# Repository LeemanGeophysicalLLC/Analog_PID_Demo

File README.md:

# Analog_PID_Demo
Demo PCB showing the use of Op-Amps to do calculus and control problems.

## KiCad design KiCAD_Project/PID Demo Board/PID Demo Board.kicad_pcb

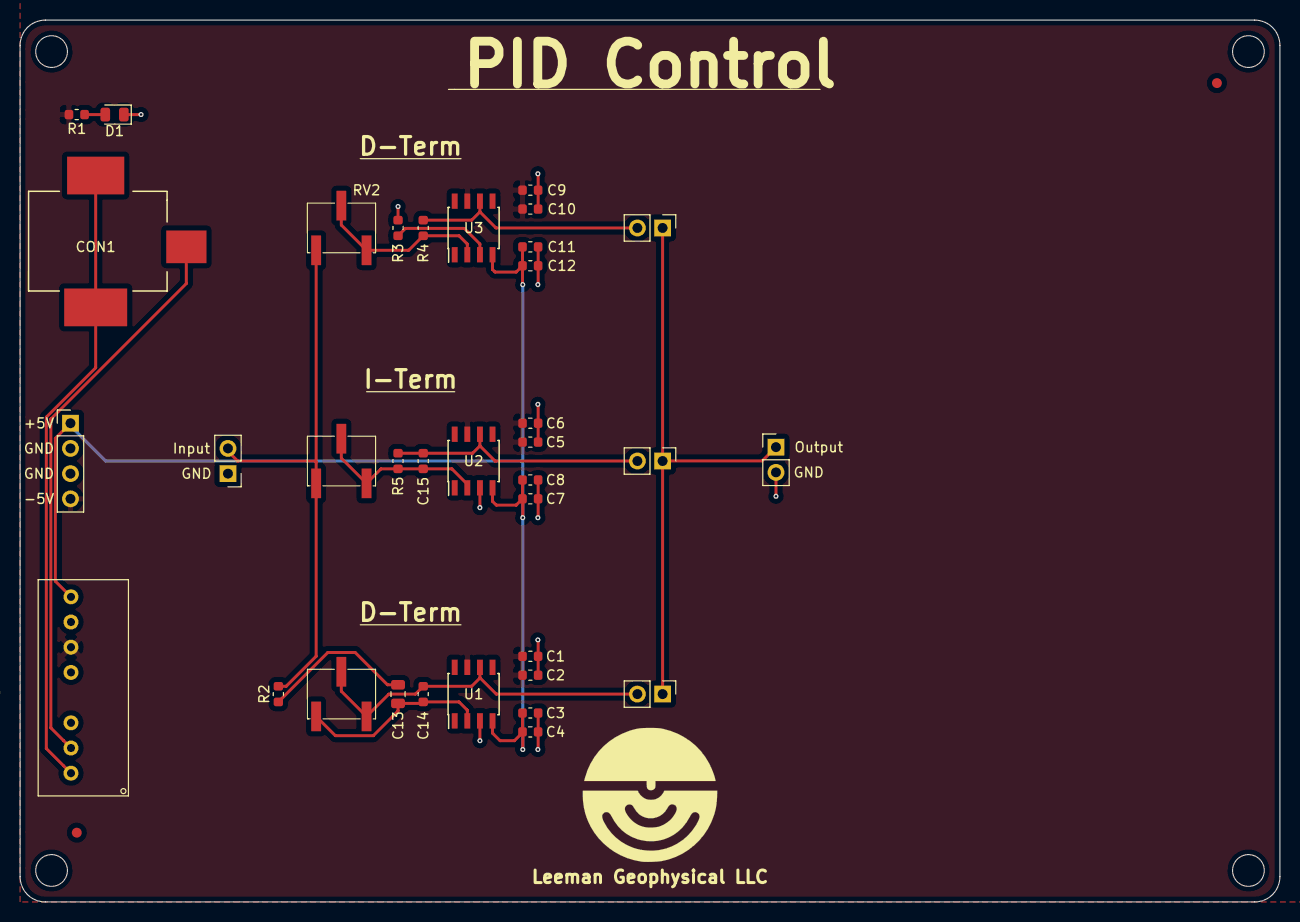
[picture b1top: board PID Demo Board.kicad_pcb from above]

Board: 2 copper layers, 127.0 x 88.9 mm, 41 parts (0 on the bottom side), 16 nets.

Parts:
C1, C4, C5, C8, C9, C12: 1-0000018
C2, C3, C6, C7, C10, C11: 1-0000007
C13: 1-0000352
C14: 1-0000322
C15: 1-0000324
CON1: 1-0000001
D1: 1-0000598
FID1, FID2: Fiducial_1mm_2mm; Fiducial_1mm_Mask2mm
H1, H2, H3, H4: M3_ISO_7380; MountingHole_3.2mm_M3_ISO7380
J1: NP_Conn_01x04; PinHeader_1x04_P2.54mm_Vertical
J2, J3, J4, J5, J6: 1-0000120
R1: 1-0000008
R2: 1-0000013
R3: 1-0000006
R4: 1-0000174
R5: 1-0000011
RV1, RV2, RV3: 1-0000337
U1, U2, U3: 1-0000419
U4: 1-0000465

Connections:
+5V: C1.2, C2.2, C5.2, C6.2, C9.2, C10.2, J1.4, R1.2, U1.7, U2.7, U3.7, U4.6
-5V: C3.2, C4.2, C7.2, C8.2, C11.2, C12.2, J1.1, U1.4, U2.4, U3.4, U4.8
GND: C1.1, C2.1, C3.1, C4.1, C5.1, C6.1, C7.1, C8.1, C9.1, C10.1, C11.1, C12.1, D1.1, J1.2, J1.3, J2.1, J6.2, R3.2, U1.3, U2.3, U4.7
unnamed: C13.1, C14.2, RV3.1, U1.2
unnamed: C13.2, R2.1
unnamed: C14.1, J3.2, RV3.2, RV3.3, U1.6
unnamed: C15.1, J4.2, R5.1, U2.6
unnamed: C15.2, R5.2, RV1.2, RV1.3, U2.2
unnamed: CON1.1, U4.2
unnamed: CON1.2, CON1.3, U4.1
unnamed: D1.2, R1.1
unnamed: J2.2, R2.2, RV1.1, RV2.1
unnamed: J3.1, J4.1, J5.1, J6.1
unnamed: J5.2, R4.1, U3.6
unnamed: R3.1, U3.3
unnamed: R4.2, RV2.2, RV2.3, U3.2

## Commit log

2021-04-26 Jonah's initial design
2021-04-26 Tweaks and production file creation.
2025-04-05 Add GERBERS
